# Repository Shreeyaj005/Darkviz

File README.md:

# Darkviz 

**Autonomous Omni-Directional Robotic System for Dark-Store Inventory Handling and Order Fulfillment**

---

## Team Details

| Sr. No. | Name of Student | Roll No. | Branch | Email ID |
|---|---|---|---|---|
| 1 | Shreeeya Jadhav | 45  | Automation and Robotics | 2023.shreeya.jadhav@ves.ac.in |
| 2 | Ayush Likhar | 11 | Automation and Robotics | 2023.ayush.likhar@ves.ac.in |
| 3 | Yash Gupta | 44 | Automation and Robotics | 2023.yash.gupta@ves.ac.in |
| 4 | Vedant Chavan | 40 | Automation and Robotics | 2023.vedant.chavan@ves.ac.in |

---
## Proposal 
https://youtu.be/7PNNnmAVzm0?si=SbWJWXD1Y0URtpTx

## Guide Details

**Project Guide: Amudha Senthilkumar**  
**Department:** Automation and Robotics  
**Institute:** VESIT, Mumbai  

---

## Problem Statement

> The aim of this project is to develop an autonomous robotic solution for inventory retrieval in quick-commerce dark stores by integrating omni-directional mobility, SLAM based navigation, and a tray based product retrieval mechanism to reduce human intervention, minimize picking errors, and improve the speed and consistency of order preparation.

---

## Abstract

### Abstract

Quick-commerce dark stores depend on rapid and accurate inventory retrieval to fulfill customer orders within short delivery times. Manual product picking can lead to delays, human errors, and increased operational effort. **DarkViz** is proposed as an autonomous robot to automate inventory retrieval and improve order preparation in dark stores.

The robot uses an **omni-directional drive system** and **SLAM (Simultaneous Localization and Mapping)** for indoor mapping, localization, and autonomous navigation. It is equipped with a **tray-based retrieval mechanism** to collect products from designated storage locations and transport them to the order-fulfillment area. Product locations can be assigned through an existing inventory management system.

The expected outcome is a functional prototype capable of accurately navigating the dark-store environment and retrieving products with minimal human intervention. The system can serve as a foundation for future **fully automated dark-store operations**, with applications in quick-commerce, warehouse automation, inventory management, and logistics.

---

## Objectives

1. To study existing inventory retrieval and automation challenges in quick-commerce dark stores and analyze available robotic solutions.
2. To design an omni-directional mobile robot with a suitable hardware, software, navigation, and tray-based product retrieval architecture.
3. To implement SLAM-based mapping and autonomous navigation along with the tray mechanism for automated product retrieval.
4. To test and validate the robot’s navigation, localization, product retrieval, and overall system performance in a simulated and physical dark-store     environment.
5. To document and present the design, implementation, results, and future scope of the DarkViz robotic system.

---

## Scope of the Project

* Development of the omni-directional robot prototype with tray based retrieval mechanism.
* Simulation of the robot and dark-store environment.
* Implementation of SLAM for mapping and localization.
* Development of autonomous navigation and robot control.
* Hardware-software integration and real-world testing.
* Performance testing of navigation and product retrieval.
* Foundation for a fully automated dark-store system.

---

## Existing System

Quick-commerce dark stores currently use inventory management software combined with manual human picking. While software manages inventory, order allocation, and picking routes, workers physically locate, retrieve, and transport products.

Limitations
- High dependence on manual labor.
- Increased risk of picking and fulfillment errors.
- Longer processing time during peak demand.
- Limited automation of inventory retrieval.
- Higher operational and labor costs.
- Poor scalability with increasing order volumes.
- Inconsistent performance due to human fatigue and errors.

---

## Proposed System

**DarkViz** is an autonomous omni-directional mobile robot designed to automate product retrieval in quick-commerce dark stores.

### How It Works

The robot uses **LiDAR-based SLAM** to map the dark store and determine its position. Once a product location is assigned by the inventory system, the robot autonomously navigates to the required shelf using **path planning and omni-directional motion**. A **motorized tray mechanism** then extends to retrieve the product and carries it to the designated order-fulfillment area.

### Major Components

* Omni-directional drive system
* LiDAR and SLAM
* ROS 2-based navigation and control
* Motor drivers and DC motors
* Automated tray retrieval mechanism
* Onboard processing unit
* Dark-store simulation environment

### Expected Benefits

* Reduced manual intervention
* Faster and more accurate product retrieval
* Reduced picking errors
* Consistent operation
* Foundation for a fully automated dark-store system

---

## System Architecture

The DarkViz architecture comprises the physical
robot hardware and two simulation environments.
Gazebo is used for LiDAR-based SLAM and navigation,
while MuJoCo is used to visualise the retractable
tray mechanism.

---

## Hardware Requirements

| Sr. No. | Component | Specification | Quantity | Purpose |
| ------- | --------- | ------------- | -------- | ------- |
| 1       |       TB6612FNG motor driver module     |   maximum voltage of 15VDC             1.2A per channel (or up to 3.2A for a short, single pulse)            |      2    |    To control the speed and direction of the robot’s DC motors by receiving control signals from the microcontroller and supplying the required current to each motor.     |
| 2       |     Pro-range Johnson motor      |      High Torque DC Motor 12V 600RPM             encoder compatible        |     3     |    To provide the required torque and rotational motion for the robot’s omni-directional wheels, enabling controlled movement in different directions.     |
| 3       |    Omni Wheels      |       Body material: Aluminium          Diameter: 60 mm.  Load capacity: 3 kg   Number of rollers: 10    Roller material: Rubber  Number of plates: 6 |    3      |    To provide omni-directional movement, allowing the robot to move forward, backward, sideways, and rotate in place for precise navigation within the dark store.     |
| 4       |     ESP WROOM 32 MCU Module Version: 1.1 microcontroller      |        generic WiFi-BT-BLE MCU module       |      1    |    To serve as the robot’s main microcontroller, processing control commands and managing motor drivers, sensors, and communication for autonomous robot operation.     |
| 5       |     raspi 4 model B      |        Broadcom BCM2711 Quad-core 64-bit Cortex-A72 @ 1.8 GHz, 4 GB LPDDR4 RAM, Wi-Fi, Bluetooth 5.0, Gigabit Ethernet, 40-pin GPIO       |      1    |    Main onboard computer for running ROS 2, SLAM, navigation algorithms, sensor processing, and high-level robot control     |
| 6       |     Battery      |       8000mah       |      1    |    To provide the primary power supply for the robot’s motors, microcontrollers, sensors, and other electronic components.     |
---

## Software Requirements

| Sr. No. | Software / Tool | Version | Purpose |
| ------- | --------------- | ------- | ------- |
| 1       |        Gazebo/Ignition         |   Gazebo Fortress      |     Simulation of the robot, sensors, environment, and navigation    |
| 2       |        RViz2        |    ROS 2 Humble     |    Visualization of SLAM maps, robot pose, LiDAR data, TF, and navigation     |
| 3       |        Ubuntu         |    22.04 LTS     |    Operating system for running ROS 2, Gazebo, RViz2, and robot software     |

---

## Technologies Used

- ROS 2 Humble – Robot software framework
- Python / C++ – Algorithm development and robot control
- SLAM – Indoor mapping and localization
- Nav2 – Autonomous navigation and path planning
- Gazebo – Robot and environment simulation
- RViz2 – Visualization and monitoring
- Raspberry Pi 4B – Main processing unit
- ESP32 – Motor and hardware control
- LiDAR – Environment sensing and mapping
- Autodesk Fusion – 3D CAD design of the robot and tray mechanism
- Embedded Systems – Motor drivers, motors, sensors, and actuator integration

---

## Methodology

Explain the step-by-step approach.

1. Literature survey
2. Problem identification
3. Requirement analysis
4. System design
5. Hardware/software development
6. Integration
7. Testing and validation
8. Documentation and publication

---

## Project Timeline

| Week / Month | Task Planned          | Status                            |
| ------------ | --------------------- | --------------------------------- |
| Week 1       | Problem finalization  |           Completed               |
| Week 2       | Literature survey     |           Completed               |
| Week 3       | Requirement analysis  |           Completed               |
| Week 4       | System design         |           In Progress             |
| Week 5       | Prototype development |           In Progress             |
| Week 6       | Testing               |           Pending                 |
| Week 7       | Documentation         |           In Progress             |
| Week 8       | Paper writing         |           In Progress                |

---

## Weekly Progress Updates

| Week | Date | Work Completed | Work Planned for Next Week | Issues / Challenges | GitHub Commit Link |
|---|---|---|---|---|---|
| Week 1 | 11-13 Aug 2026 | Set up the Gazebo warehouse environment and integrated the omni-wheel robot. Added initial CAD files and project documentation. | Implement SLAM and autonomous navigation. | - **Gazebo Simulation:** Encountered server-side issues while launching Gazebo, requiring troubleshooting of the simulation environment.- **ROS 2 Integration:** Learning the ROS 2 filesystem structure and package organization to configure and launch the robot simulation.- **Omni-Wheel Kinematics:** Working on simulating the robot using ROS 2 control interfaces, with motion control based on kiwi-drive kinematics. | [Commits](https://github.com/Shreeyaj005/Darkviz/commits/main/?since=2026-08-11&until=2026-08-13) |
| Week 2 | 14-22 Aug 2026 | Integrated SLAM, omni-drive control and autonomous navigation. Added coordinate-based navigation and waypoint selection. | Improve navigation and robot control. | **Map Generation and Optimization**: Studying the effects of LiDAR data, sensor noise, map resolution, and SLAM parameters on map quality.-**Map Acquisition**: Exploring how to generate, save, and reload maps for autonomous navigation.-**Robot–Map Coordination**: Understanding coordinate frames, TF transformations, localization, and odometry to align the robot's pose with the map.  | [Commits](https://github.com/Shreeyaj005/Darkviz/commits/main/?since=2026-08-14&until=2026-08-22) |
| Week 3 | 31 Aug-5 Sep 2026 | Added simulation documentation and migrated the ROS 2 setup to Humble. Updated project setup instructions. | Refine ROS 2 integration and robot control. | ROS 2 package and dependency compatibility. | [Commits](https://github.com/Shreeyaj005/Darkviz/commits/main/?since=2026-08-31&until=2026-09-05) |
| Week 4 | 22-23 Sep 2026 | started with the hardware design, tested motors with driver individually | Refine robot control and document hardware connections. | Odometry accuracy and motion control debugging. | [Commits](https://github.com/Shreeyaj005/Darkviz/commits/main/?since=2026-09-22&until=2026-09-23) |
| Week 5 | Hardware Design & Testing | designed the robot hardware, 3D-printed structural components and omni-wheel couplers, and individually tested the motors with their motor drivers. | Refine the mechanical design, verify motor-driver functionality, and prepare for hardware integration. | - **Motor Power Testing:** Observed voltage drops while operating the motors at a 6 V supply, despite their 12 V maximum rated voltage, highlighting the need to investigate power supply limitations and current demand under load.<br>- **Mechanical Design Optimization:** Explored a sleek, warehouse-oriented robot design focused on compactness and efficient movement in constrained spaces.<br>- **Load-Bearing Mobility:** Evaluated design considerations for moving loads smoothly using omni-wheels while maintaining stability and maneuverability.<br>- **Design Simplification:** Reassessed the initial mechanical design to reduce complexity and make fabrication, assembly, and integration easier. <br> Resolve electrical faults, establish reliable power distribution, and ensure consistent PWM-based motor control through the ESP32. - **Perfboard Assembly:** Implemented the motor control circuit on a perfboard and tested individual motor operation.<br>- **Power Distribution:** Investigated power delivery issues affecting motor and controller operation.<br>- **Short-Circuit Detection:** Identified and troubleshot short circuits and wiring faults in the assembled connections.<br>- **PWM Signal Debugging:** Investigated issues with PWM signal transmission from the ESP32 to the motor drivers.<br>- **ESP32 Integration:** Troubleshot controller power and connection issues to improve reliable communication with the motor drivers. | [Commits](https://github.com/Shreeyaj005/Darkviz/commits/main/?since=2026-10-08&until=2026-10-23) |
| Week 6 | 24-28 Oct 2026 | Drafted the Kiwi-drive PCB and circuit schematic, documented motor and encoder connections, and updated the simulation model to match the physical robot. | Optimize PCB size, improve connection accessibility, and develop a reliable layout for hardware integration. | - **PCB Miniaturization:** Working on reducing PCB dimensions while maintaining sufficient spacing and practical component placement.<br>- **Connection Accessibility:** Organizing connectors and pin assignments to simplify wiring, assembly, and debugging.- **PCB Design Tools:** Learning KiCad for schematic design, footprint assignment, component placement, and PCB routing.<br>- **Hardware Integration:** Addressing component compatibility, pin mapping, power distribution, and grounding requirements for reliable operation. | [Commits](https://github.com/Shreeyaj005/Darkviz/commits/main/?since=2026-10-24&until=2026-10-28) |
| Week 7 | 29 Oct-4 Nov 2026 | Consolidated project documentation, reviewed the simulation and hardware implementation, and prepared review materials. | Present project progress and incorporate review feedback. | Final documentation and integration checks. | [Repository](https://github.com/Shreeyaj005/Darkviz) |
| Week 8 | 5 Nov 2026 | Presenting the project implementation, hardware progress and simulation results during the scheduled review. | Incorporate feedback and plan the next development phase. | Pending review feedback. | [Repository](https://github.com/Shreeyaj005/Darkviz) |

Upcoming Milestone: Project Progress Review – 5 November 2026.

---

## Design Files

Upload and link all design files here.

| File Type       | File Name / Link | Description |
| --------------- | ---------------- | ----------- |
| CAD Model       | Darkviz/hardware | Folder contains .step and .stl files for model  |
| Circuit Diagram |                  |             |
| PCB Design      |                  |             |
| Flowchart       |                  |             |
| Simulation File |simulation/kiwi_robot/scripts/autonomous_controller.py  | Autonomous controller script for the robot to explore environment. Run slam.launch.py before running the script|

---

## Circuit Diagram

Add circuit diagram image here.

```markdown

```

---

## Flowchart / Algorithm

### Algorithm

1. **Initialize System** : Start ROS 2 nodes, robot model, sensors, and simulation environment.
2. **Map Environment** : Use LiDAR and odometry with SLAM Toolbox to generate a 2D map of the dark-store.
3. **Localize Robot**: Estimate the robot's position within the generated map.
4. **Set Target** : Receive the target shelf or order-fulfillment location.
5. **Plan Path** : Use Nav2 to generate a collision-free path to the target.
6. **Navigate** : Generate velocity commands and move the omni-directional robot toward the target.
7. **Avoid Obstacles** : Continuously process LiDAR data and update navigation commands when obstacles are detected.
8. **Complete Task** : Stop at the target location or proceed to the next assigned target.
9. **Repeat** : Continue the process until all assigned tasks are completed.

---

## Implementation Details

DarkViz is implemented as a ROS 2 Humble-based autonomous omni-directional robotic system designed for inventory handling and order fulfillment in a dark-store environment. The system combines robot modelling, LiDAR-based perception, odometry, 2D SLAM, autonomous navigation, and motion control within a Gazebo simulation.

### Hardware Implementation

Write details about connections, components, power supply, sensors, actuators, PCB, enclosure, etc.

### Software Implementation

DarkViz is implemented using **ROS 2 Humble** with Gazebo for simulation and RViz2 for visualization. The robot is modelled using **URDF/Xacro**, while Python and C++ ROS 2 nodes handle control, odometry, sensor processing, and navigation.

* **SLAM Toolbox**: 2D mapping and localization using LiDAR and odometry
* **Nav2**: autonomous path planning and obstacle avoidance
* **ROS 2 Topics & TF**: communication and coordinate-frame management
* **Gazebo**: dark-store environment and robot simulation
* **RViz2**: visualization of maps, LiDAR, TF, and navigation
* **Python/C++**: robot control and processing nodes

The overall pipeline is:

**LiDAR + Odometry → SLAM/Localization → Navigation → `/cmd_vel` → Omni-directional Robot Motion**

---

## Code Structure

```text
Darkviz/
│
├── docs/
│   └── literarture_survey.md
│
├── hardware/
│   ├── darkviz_base.f3d
│   ├── darkviz_base.stl
│   ├── final design.step
│   └── hardware.md
│
├── images/
│   ├── 3d_printed_prototype_assembled.jpg
│   ├── 3d_printed_prototype_top_view.jpg
│   ├── Ideation.jpeg
│   ├── images.md
│   └── Linear Guide Rail.png
│
├── simulation/
│   ├── kiwi_robot/
│   │   ├── CMakeLists.txt
│   │   ├── package.xml
│   │   ├── config/
│   │   ├── launch/
│   │   ├── scripts/
│   │   ├── urdf/
│   │   └── worlds/
│   │
│   └── README.md
│
├── software/
│   ├── kiwi_drive_control.ino
│   └── software.md
│
├── reference/
│   └── paper.md
│
└── README.md```

---

## How to Run the Project

### Step 1: Clone the Repository

```bash
git clone https://github.com/Shreeyaj005/Darkviz.git
cd Darkviz/software/simulation
```

### Step 2: Install Dependencies

```bash
source /opt/ros/humble/setup.bash
colcon build
source install/setup.bash
```

### Step 3: Launch Simulation

```bash
ros2 launch kiwi_robot gazebo.launch.py
```
This launches the DarkViz robot and the simulated dark-store environment in Gazebo.

### Step 4: Run SLAM
In a new terminal:
```bash
cd ~/Darkviz/software/simulation
source /opt/ros/humble/setup.bash
source install/setup.bash
ros2 launch kiwi_robot slam.launch.py
```
RViz2 can be used to visualize the LiDAR data, TF frames, and generated 2D map.

### Step 5: Control and Navigate the Robot
The robot can be controlled using the available ROS 2 control/navigation nodes. Navigation commands are published through /cmd_vel, while LiDAR and odometry provide feedback for localization and obstacle avoidance.

### Expected Output
The Gazebo simulation should start with the DarkViz omni-directional robot inside the simulated dark-store. The robot's LiDAR and odometry data should be available through ROS 2 topics, and SLAM should progressively generate a 2D map of the environment.

---

## Testing and Results

| Test No. | Test Description | Expected Result | Actual Result | Status      |
| -------- | ---------------- | --------------- | ------------- | ----------- |
| 1        |                  |                 |               | Pass / Fail |
| 2        |                  |                 |               | Pass / Fail |
| 3        |                  |                 |               | Pass / Fail |

---

## Result Images / Videos

Video Link:
https://youtu.be/ZUh2bRQQ1O0
---

## Applications

1. Dark-Store Order Fulfillment: Autonomous movement between storage shelves and order collection areas.
2. Inventory Management: Automated navigation for inventory inspection, stock monitoring, and shelf-level data collection.
3. Warehouse Automation: Autonomous transportation of goods between storage and packing areas.

---

## Advantages

1. Omni-Directional Mobility: Enables lateral movement and precise positioning in narrow aisles.
2. Autonomous Navigation: Uses SLAM and Nav2 for mapping, localization, path planning, and obstacle avoidance.
3. Modular ROS 2 Architecture: Individual perception, control, and navigation components can be developed and modified independently.
4. Simulation-Based Development: Gazebo enables testing and validation of the robotic system before deployment on physical hardware.
---

## Limitations
1. Simulation Environment: Current implementation is primarily validated in simulation and may require further testing on physical hardware.
2. 2D Perception: The current LiDAR-based system provides primarily 2D environmental information.
3. Simplified Inventory Handling: Physical picking, gripping, and placement mechanisms are not yet fully integrated.
4. Environmental Dependence: Navigation performance can be affected by dynamic obstacles, sensor noise, and changes in the store layout.

---

## Future Scope
1. Automated Picking: Add robotic manipulation for shelf-level item detection, picking, and placement.
2. Computer Vision Integration: Use cameras and vision models for product recognition, shelf monitoring, and inventory tracking.
3. Multi-Robot Coordination: Extend the system to coordinate multiple robots for parallel order fulfillment and inventory operations.

---

## Research Paper / Publication

| Item                      | Details                                                   |
| ------------------------- | --------------------------------------------------------- |
| Paper Title               | DarkViz: Design and Performance Evaluation of a Three-Wheeled Omni-Directional Mobile Robot for Autonomous Navigation in Space-Constrained Darkstores     |
| Conference / Journal Name |                                                           |
| Paper Status              |  Drafting                                                 |
| Submission Date           |                                                           |
| Paper Link                |                                                           |

---

## References
```text
[1] L. Tagliavini, G. Colucci, A. Botta, P. Cavallone, L. Baglieri, and G. Quaglia, "Wheeled Mobile Robots: State of the Art Overview and Kinematic Comparison Among Three Omnidirectional Locomotion Strategies," Journal of Intelligent & Robotic Systems, vol. 106, Art. no. 57, 2022, doi: 10.1007/s10846-022-01745-7.

[2] D. Martínez, E. Rubies, R. Bitriá, and J. Palacín, "Evaluation and Correction of Systematic Motion Errors in a Compact Three-Wheeled Omnidirectional Platform Based on Servomotors," Applied Sciences, vol. 15, no. 19, Art. no. 10700, 2025, doi: 10.3390/app151910700.

[3] J. Moreno, E. Clotet, R. Lupiañez, M. Tresanchez, D. Martínez, T. Pallejà, J. Casanovas, and J. Palacín, "Design, Implementation and Validation of the Three-Wheel Holonomic Motion System of the Assistant Personal Robot (APR)," Sensors, vol. 16, no. 10, Art. no. 1658, 2016, doi: 10.3390/s16101658.

[4] L. Li, L. Schulze, and K. Kalavadia, "Promising SLAM Methods for Automated Guided Vehicles and Autonomous Mobile Robots," Procedia Computer Science, vol. 232, pp. 2867–2874, 2024, doi: 10.1016/j.procs.2024.02.103.

[5] R. Keith and H. M. La, "Review of Autonomous Mobile Robots for the Warehouse Environment," arXiv preprint arXiv:2406.08333, 2024. [Online]. Available: https://arxiv.org/abs/2406.08333.

[6] G. Fragapane, R. de Koster, F. Sgarbossa, and J. O. Strandhagen, "Planning and Control of Autonomous Mobile Robots for Intralogistics: Literature Review and Research Agenda," European Journal of Operational Research, vol. 294, no. 2, pp. 405–426, 2021, doi: 10.1016/j.ejor.2021.01.019.

[7] K. Azadeh, R. de Koster, and D. Roy, "Robotized and Automated Warehouse Systems: Review and Recent Developments," Transportation Science, vol. 53, no. 4, pp. 917–945, 2019, doi: 10.1287/trsc.2018.0873.

[8] Í. R. da Costa Barros and T. P. Nascimento, "Robotic Mobile Fulfillment Systems: A Survey on Recent Developments and Research Opportunities," Robotics and Autonomous Systems, vol. 137, Art. no. 103729, 2021, doi: 10.1016/j.robot.2021.103729.

[9] H. Taheri, B. Qiao, and N. Nurre, "Kinematic Model of a Three-Wheeled Omnidirectional Mobile Robot," The International Journal of Advanced Manufacturing Technology, vol. 78, pp. 1563–1571, 2015, doi: 10.1007/s00170-014-6761-3.

[10] R. Rojas, "Kinematics of Omnidirectional Robots," Freie Universität Berlin, Technical Report, 2005.

[11] R. Siegwart, I. R. Nourbakhsh, and D. Scaramuzza, Introduction to Autonomous Mobile Robots, 2nd ed. Cambridge, MA, USA: MIT Press, 2011.
```

---

## Repository Update Guidelines

Each student team must update the GitHub repository regularly.

Minimum expected updates:

* Update README every week.
* Push code changes regularly.
* Upload circuit diagrams, CAD files, PCB files, reports and presentations.
* Add weekly progress in the progress table.
* Maintain proper folder structure.
* Do not upload unnecessary temporary files.
* Each major update should have a meaningful commit message.

Example commit messages:

```text
Added problem statement and objectives
Updated system architecture diagram
Added sensor interfacing code
Updated weekly progress for Week 3
Added testing results and prototype images
```

---

## Declaration

We declare that this project work is carried out by our team as part of the BE Capstone Project. The work will be regularly updated on GitHub and all references used will be properly cited.

---

## License

This project is for academic use only.

Optional:

```text
MIT License / Creative Commons / Institute Use Only
```

```
```

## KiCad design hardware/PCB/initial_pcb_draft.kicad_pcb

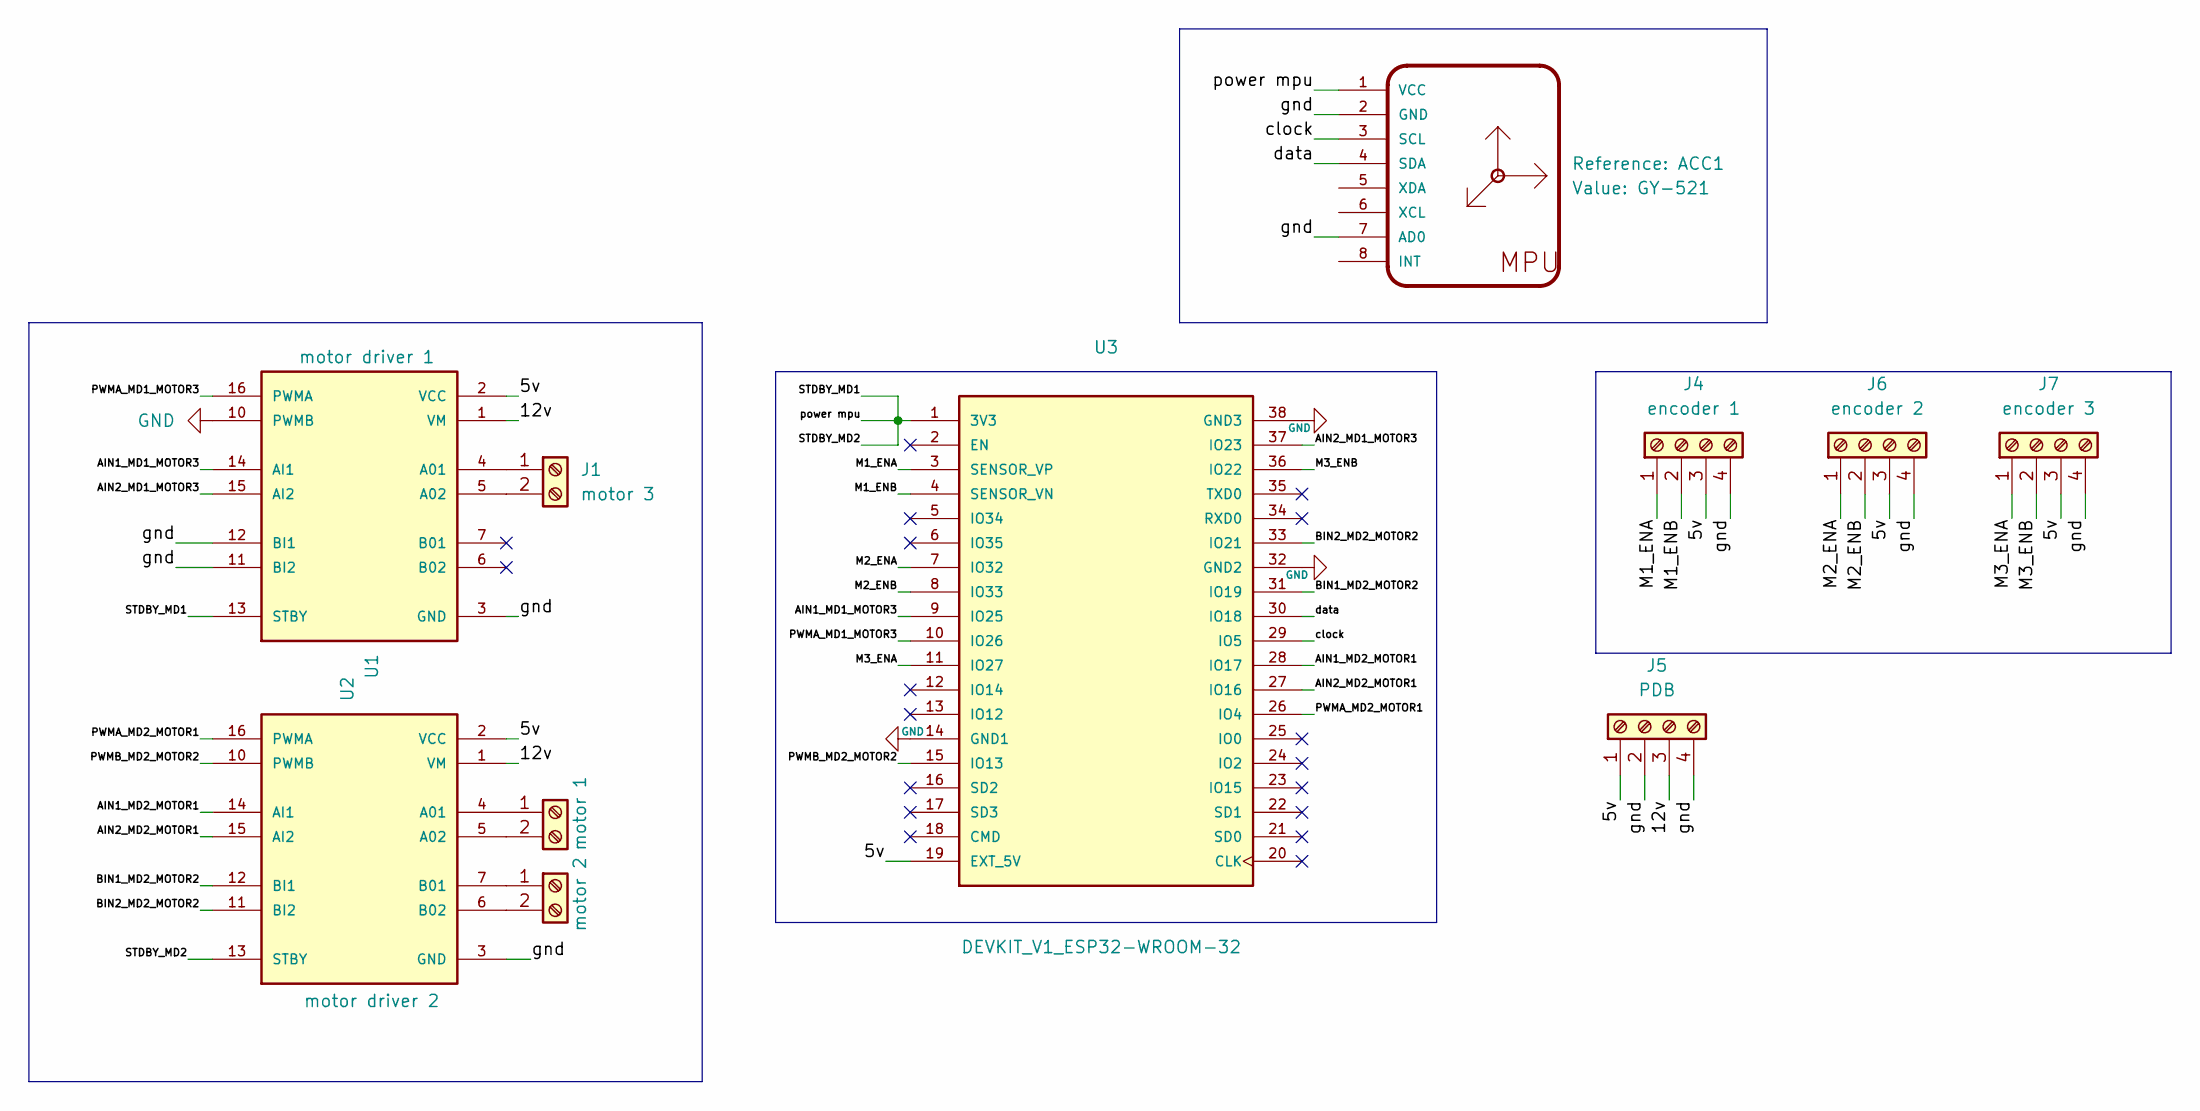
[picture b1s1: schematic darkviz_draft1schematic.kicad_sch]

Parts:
ACC1: GY-521; PinHeader_1x08_P2.54mm_Vertical
J1: motor 3; TerminalBlock_Phoenix_MKDS-1,5-2-5.08_1x02_P5.08mm_Horizont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
J2: motor 2; TerminalBlock_Phoenix_MKDS-1,5-2-5.08_1x02_P5.08mm_Horizont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
J3: motor 1; TerminalBlock_Phoenix_MKDS-1,5-2-5.08_1x02_P5.08mm_Horizont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
J4: encoder 1; PinHeader_1x04_P2.54mm_Vertical
J5: PDB; PinHeader_1x04_P2.54mm_Vertical
J6: encoder 2; PinHeader_1x04_P2.54mm_Vertical
J7: encoder 3; PinHeader_1x04_P2.54mm_Vertical
U1: motor driver 1; MODULE_ROB-14450; PARTREV 11-13-17
U2: motor driver 2; MODULE_ROB-14450; PARTREV 11-13-17
U3: DEVKIT_V1_ESP32-WROOM-32; MODULE_DEVKIT_V1_ESP32-WROOM-32; PARTREV N/A

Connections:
/5v: J4.3, J5.1, J6.3, J7.3, U1.2 (VCC), U2.2 (VCC), U3.19 (EXT_5V)
/12v: J5.3, U1.1 (VM), U2.1 (VM)
/AIN1_MD1_MOTOR3: U1.14 (AI1), U3.9 (IO25)
/AIN1_MD2_MOTOR1: U2.14 (AI1), U3.28 (IO17)
/AIN2_MD1_MOTOR3: U1.15 (AI2), U3.37 (IO23)
/AIN2_MD2_MOTOR1: U2.15 (AI2), U3.27 (IO16)
/BIN1_MD2_MOTOR2: U2.12 (BI1), U3.31 (IO19)
/BIN2_MD2_MOTOR2: U2.11 (BI2), U3.33 (IO21)
/M1_ENA: J4.1, U3.3 (SENSOR_VP)
/M1_ENB: J4.2, U3.4 (SENSOR_VN)
/M2_ENA: J6.1, U3.7 (IO32)
/M2_ENB: J6.2, U3.8 (IO33)
/M3_ENA: J7.1, U3.11 (IO27)
/M3_ENB: J7.2, U3.36 (IO22)
/PWMA_MD1_MOTOR3: U1.16 (PWMA), U3.10 (IO26)
/PWMA_MD2_MOTOR1: U2.16 (PWMA), U3.26 (IO4)
/PWMB_MD2_MOTOR2: U2.10 (PWMB), U3.15 (IO13)
/STDBY_MD1: ACC1.1 (VCC), U1.13 (STBY), U2.13 (STBY), U3.1 (3V3)
/clock: ACC1.3 (SCL), U3.29 (IO5)
/data: ACC1.4 (SDA), U3.30 (IO18)
GND: ACC1.2 (GND), ACC1.7 (AD0), J4.4, J5.2, J5.4, J6.4, J7.4, U1.3 (GND), U1.8 (GND), U1.9 (GND), U1.10 (PWMB), U1.11 (BI2), U1.12 (BI1), U2.3 (GND), U2.8 (GND), U2.9 (GND), U3.14 (GND1), U3.32 (GND2), U3.38 (GND3)
unnamed: J1.1, U1.4 (A01)
unnamed: J1.2, U1.5 (A02)
unnamed: J2.1, U2.7 (B01)
unnamed: J2.2, U2.6 (B02)
unnamed: J3.1, U2.4 (A01)
unnamed: J3.2, U2.5 (A02)

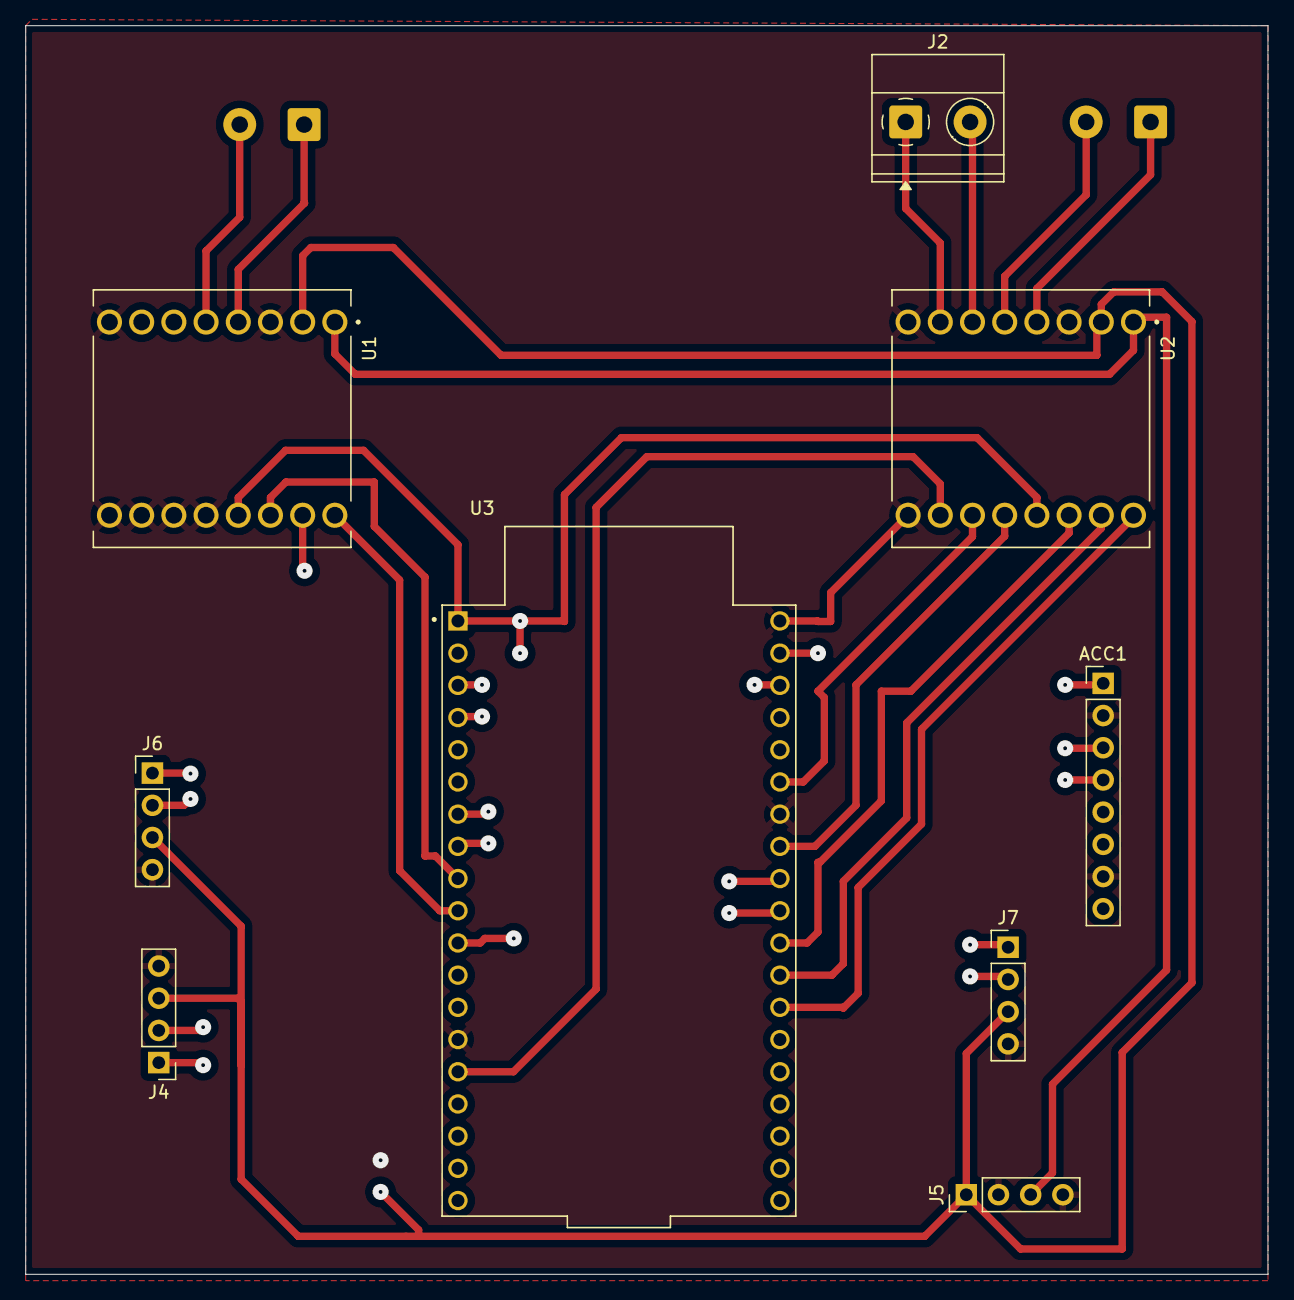
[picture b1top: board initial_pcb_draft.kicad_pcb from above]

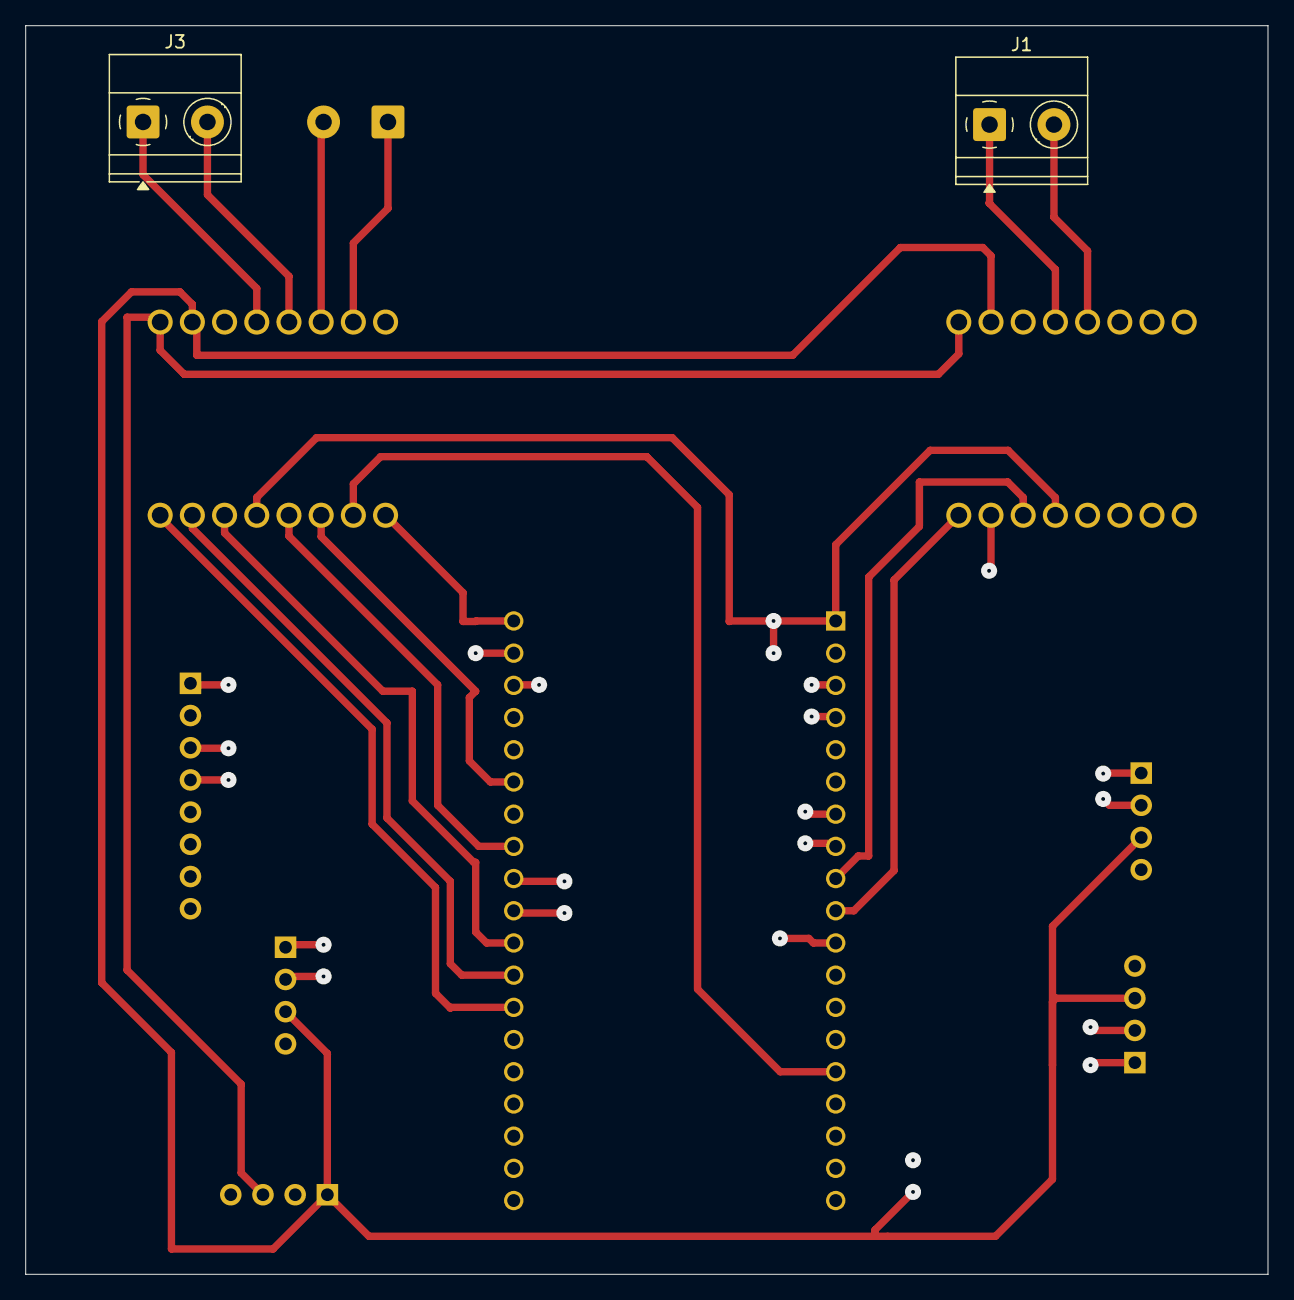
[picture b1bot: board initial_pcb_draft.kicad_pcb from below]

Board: 2 copper layers, 98.0 x 98.5 mm, 11 parts (2 on the bottom side), 27 nets.
